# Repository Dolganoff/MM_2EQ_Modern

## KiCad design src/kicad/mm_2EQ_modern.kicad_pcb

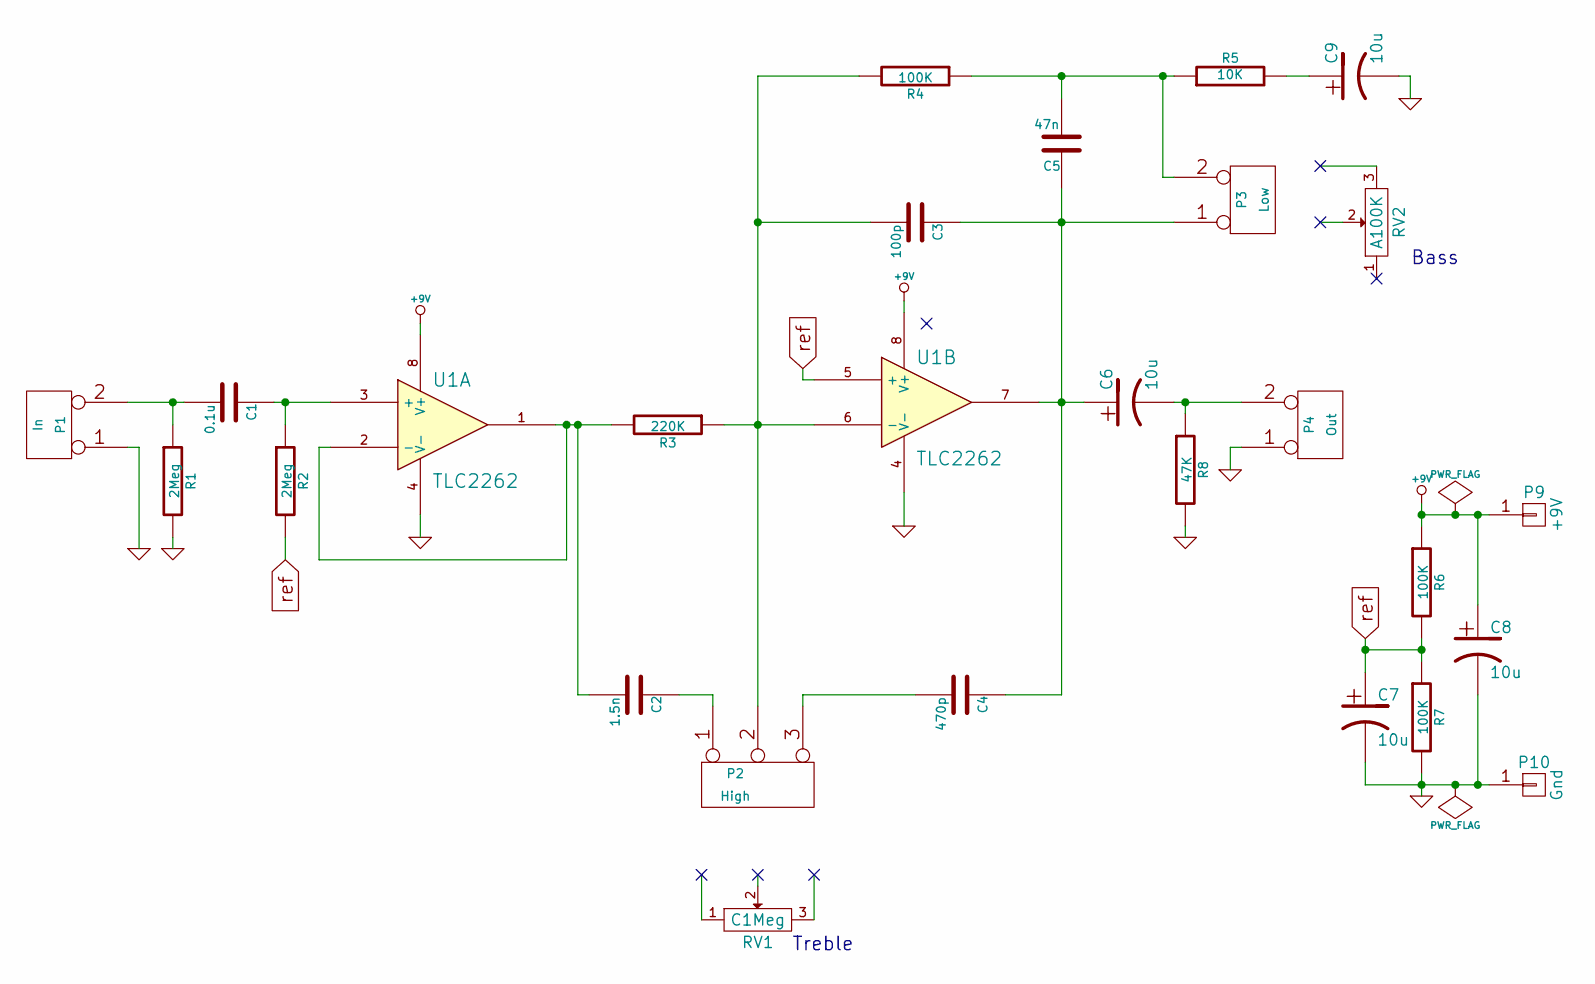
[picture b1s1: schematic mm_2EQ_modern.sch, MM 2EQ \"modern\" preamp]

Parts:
C1: 0.1u; C2-LARGE_PADS
C2: 1.5n; C2-LARGE_PADS
C3: 100p; C2-LARGE_PADS
C4: 470p; C2-LARGE_PADS
C5: 47n; C2-LARGE_PADS
C6, C7, C8, C9: 10u; C1V5-LARGE_PADS
P1: In; SIL-2-LARGE_PADS
P2: High; SIL-3-LARGE_PADS
P3: Low; SIL-2-LARGE_PADS
P4: Out; SIL-2-LARGE_PADS
P9: +9V; SolderWirePad_single_0-8mmDrill
P10: Gnd; SolderWirePad_single_0-8mmDrill
R1, R2: 2Meg; R3-LARGE_PADS
R3: 220K; R3-LARGE_PADS
R4, R6, R7: 100K; R3-LARGE_PADS
R5: 10K; R3-LARGE_PADS
R8: 47K; R3-LARGE_PADS
RV1: C1Meg
RV2: A100K
U1: TLC2262; DIP-8_LARGE_PADS

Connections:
+9V: C8.1, P9.1, R6.1, U1.8 (V+)
GND: C7.2, C8.2, C9.2, P1.1, P4.1, P10.1, R1.2, R7.2, R8.2, U1.4 (V-)
unnamed: C1.1, R2.1, U1.3 (+)
unnamed: C1.2, P1.2 (PM), R1.1
unnamed: C2.1, P2.1
unnamed: C2.2, R3.2, U1.1, U1.2 (-)
unnamed: C3.1, C4.1, C5.1, C6.1, P3.1, U1.7
unnamed: C3.2, P2.2 (PM), R3.1, R4.2, U1.6 (-)
unnamed: C4.2, P2.3
unnamed: C5.2, P3.2 (PM), R4.1, R5.1
unnamed: C6.2, P4.2 (PM), R8.1
unnamed: C9.1, R5.2
ref: C7.1, R2.2, R6.2, R7.1, U1.5 (+)

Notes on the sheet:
Treble
Bass

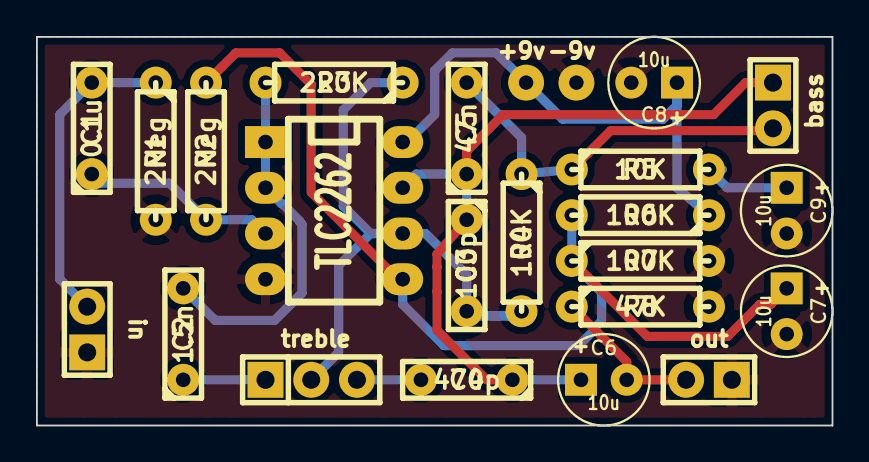
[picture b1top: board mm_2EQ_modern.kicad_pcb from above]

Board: 2 copper layers, 44.2 x 21.6 mm, 24 parts (0 on the bottom side), 13 nets.

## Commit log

2014-11-30 :confetti_ball: Added .gitattributes & .gitignore files
2014-11-30 cleanup
2014-11-30 modify simulations
2014-11-30 netlist delete
2014-11-30 routing first pass
2014-11-30 routing second pass
2014-12-09 minor changes
